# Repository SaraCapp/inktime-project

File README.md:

Schematicul meu este destul de bine organizat si se vede ca am gandit proiectul pe blocuri. Se distinge clar zona de microcontroller, partea de alimentare, zona de debug si fuel gauge-ul, ceea ce face schema mai usor de urmarit. Per total consider ca are o structura logica si se intelege destul de bine cum comunica componentele intre ele.
Proiectul meu este un dispozitiv bazat pe nRF52840. Acesta controleaza mai multe componente precum display-ul e-paper, IMU-ul, partea de haptic si fuel gauge-ul pentru baterie.
Componenta principala este nRF52840. Acesta comunica cu restul componentelor si controleaza functionarea intregului sistem.
Blocurile principale din proiect sunt:
- nRF52840
- display e-paper
- IMU
- haptic driver
- fuel gauge
- power management
- baterie Li-Po
- USB-C
Fisierele gerber bom si pick and place se gasesc in manufacturing
nRF52840 este conectat la componente prin interfete de tip I2C, SPI, GPIO si SWD.

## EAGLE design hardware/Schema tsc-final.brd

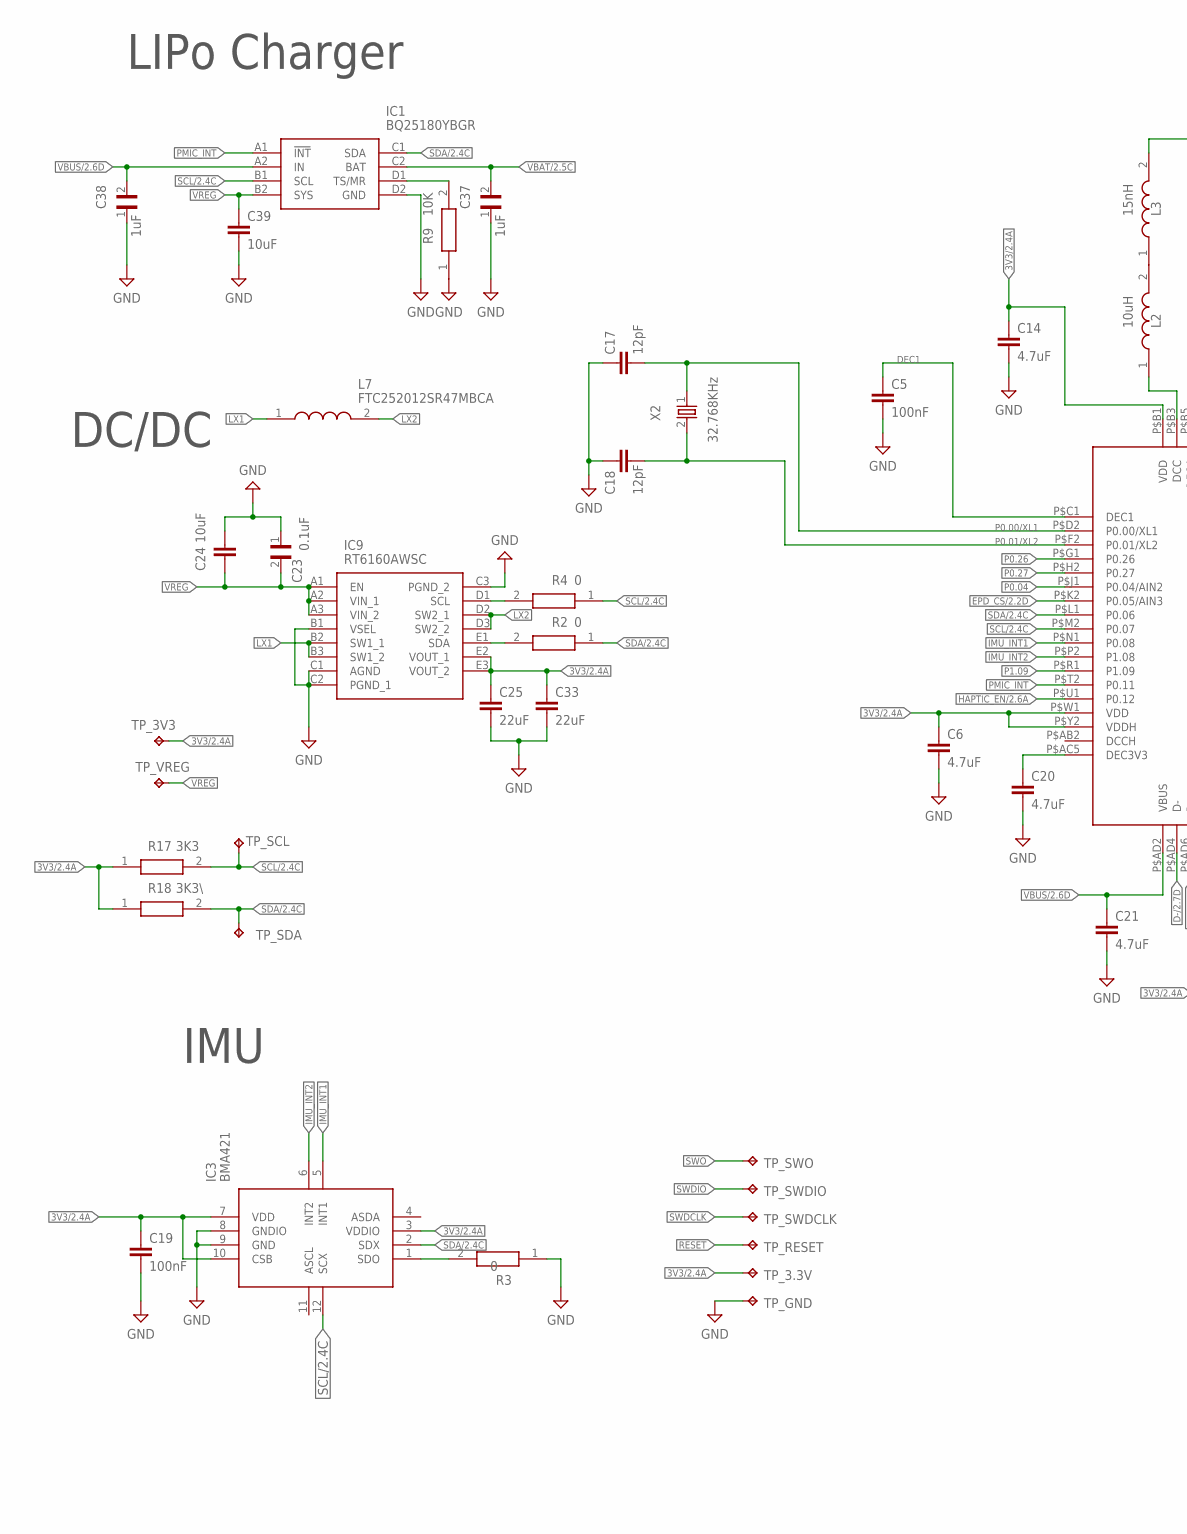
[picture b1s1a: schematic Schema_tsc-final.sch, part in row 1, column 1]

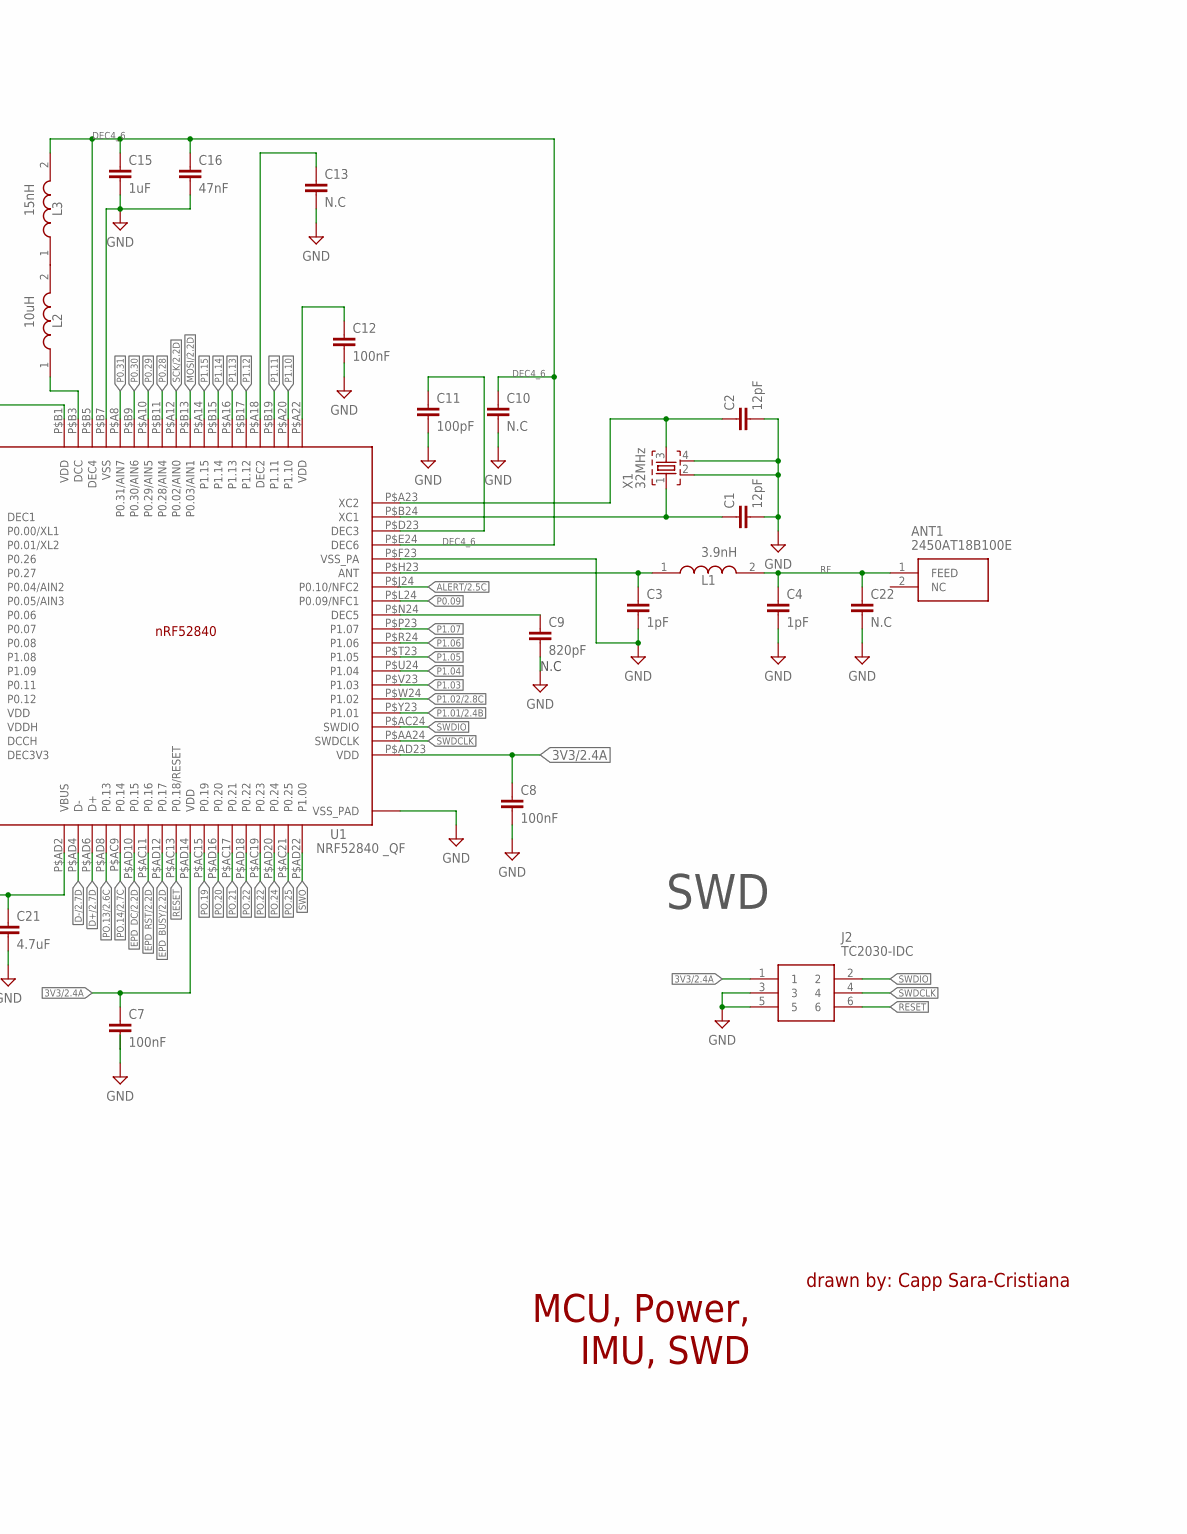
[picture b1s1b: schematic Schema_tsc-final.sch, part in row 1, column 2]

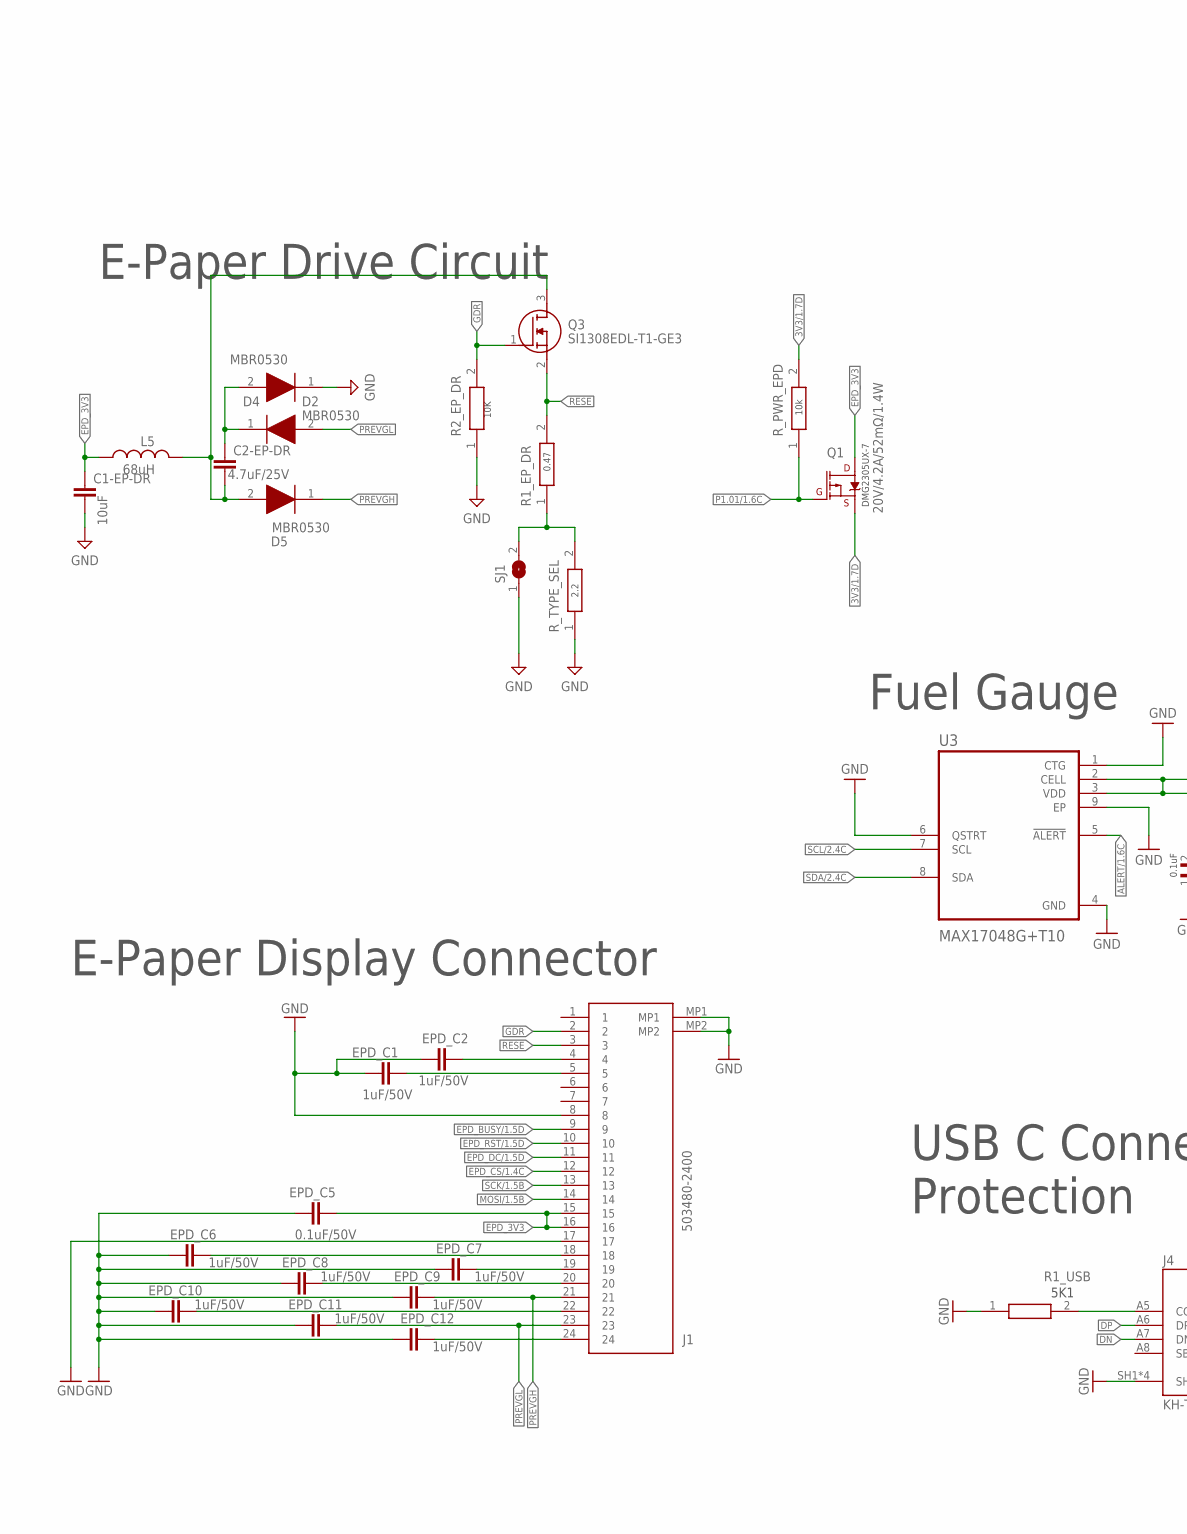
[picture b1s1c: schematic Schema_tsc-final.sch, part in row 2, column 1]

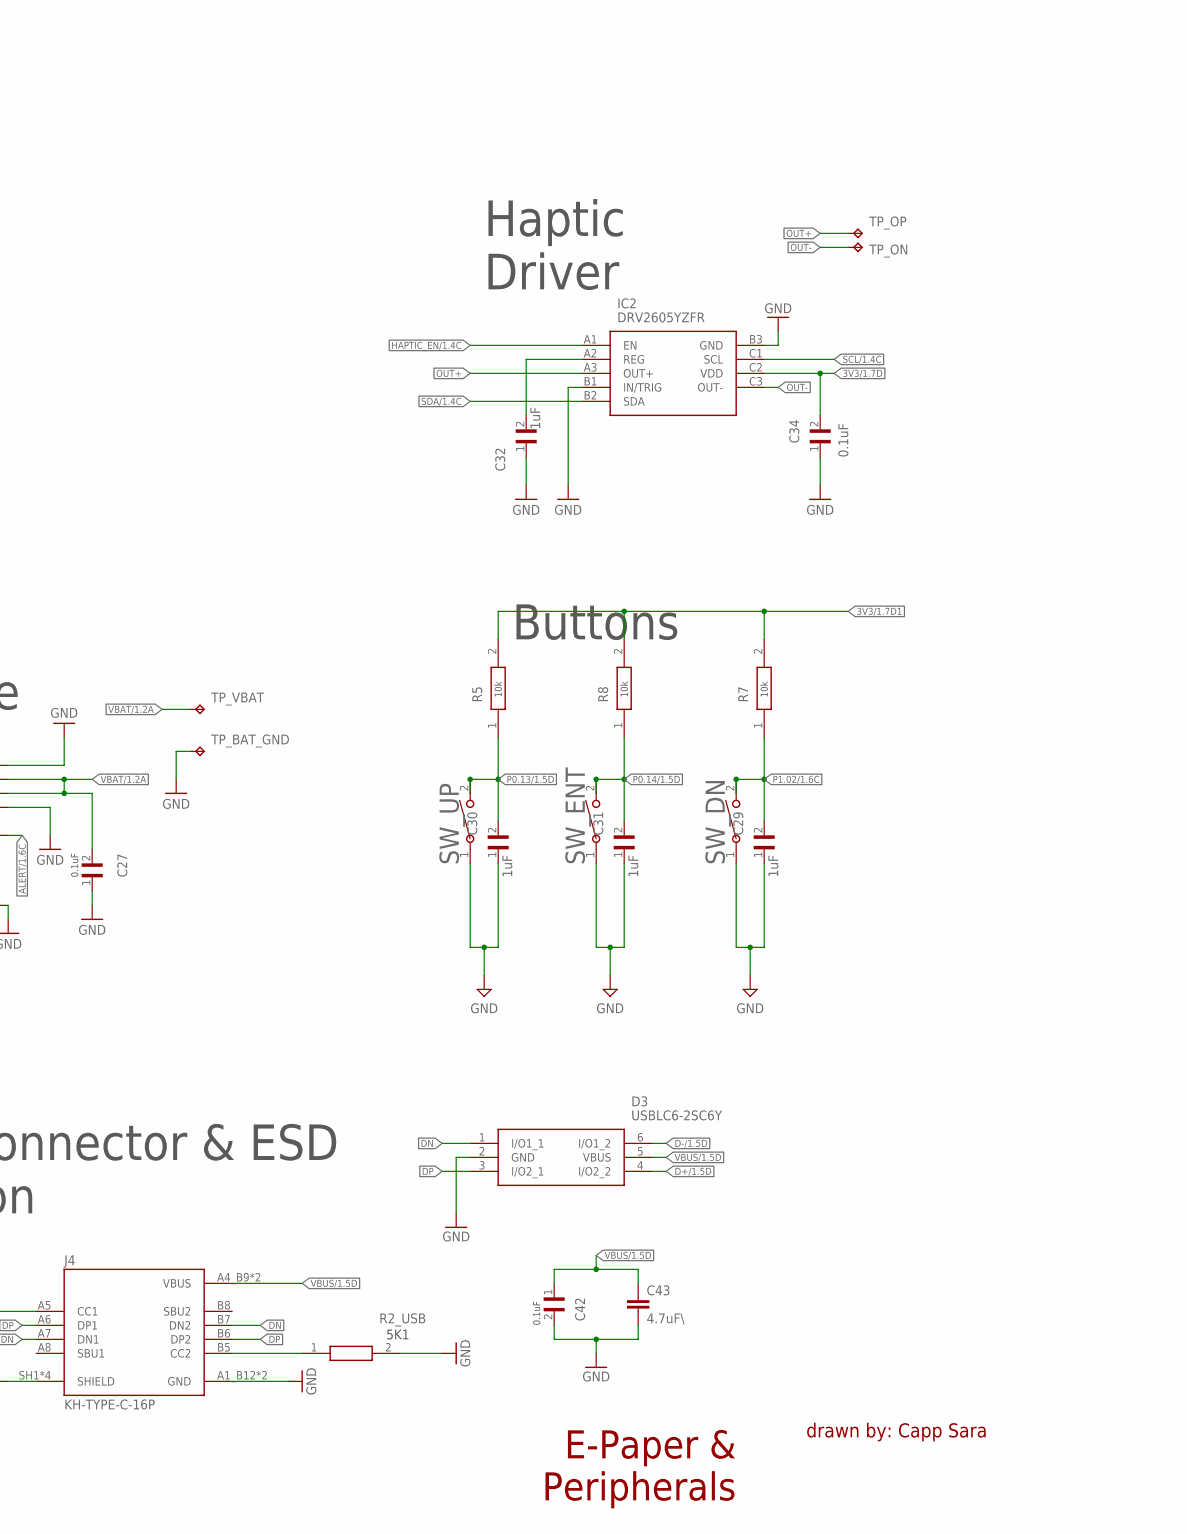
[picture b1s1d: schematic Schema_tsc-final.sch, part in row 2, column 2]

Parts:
ANT1: 2450AT18B100E; 2450AT18B100E_ANTC3216X140N
C1, C2, C17, C18: 12pF; NORDIC_NRF_3_RESC0201_L
C1-EP-DR, C24, C39: 10uF; NORDIC_NRF_3_RESC0402_L
C2-EP-DR: 4.7uF/25V; NORDIC_NRF_3_RESC0402_L
C3, C4: 1pF; NORDIC_NRF_3_RESC0201_L
C5, C7, C8, C12, C19: 100nF; NORDIC_NRF_3_RESC0201_L
C6, C14, C20, C21: 4.7uF; NORDIC_NRF_3_RESC0402_L
C9: 820pF; NORDIC_NRF_3_RESC0201_L
C10, C13: N.C; NORDIC_NRF_3_RESC0201_L
C11: 100pF; NORDIC_NRF_3_RESC0201_L
C15: 1uF; NORDIC_NRF_3_RESC0402_L
C16: 47nF; NORDIC_NRF_3_RESC0201_L
C22: N.C; NORDIC_NRF_3_RESC0402_L
C23, C42: 0.1uF; GRM011R60J152KE01L_2_CAPC0201X13N
C25, C33: 22uF; NORDIC_NRF_3_RESC0402_L
C27, C34: 0.1uF; GRM011R60J152KE01L_1_0201
C29, C30, C31, C37, C38: 1uF; GRM011R60J152KE01L_2_CAPC0201X13N
C32: 1uF; GRM011R60J152KE01L_1_0201
C43: 4.7uF\; NORDIC_NRF_3_RESC0402_L
D2, D4, D5: MBR0530; ESP32_C6_LIBRARY_5_SOD3716X135N
D3: USBLC6-2SC6Y; ESP32_C6_LIBRARY_3_SOT95P280X145-6N
EPD_C1, EPD_C2, EPD_C6, EPD_C7, EPD_C8, EPD_C9, EPD_C10, EPD_C11, EPD_C12: 1uF/50V; NORDIC_NRF_3_RESC0402_L
EPD_C5: 0.1uF/50V; NORDIC_NRF_3_RESC0201_L
IC1: BQ25180YBGR; BQ25180YBGR_BGA8C40P2X4_100X155X50
IC2: DRV2605YZFR; DRV2605YZFR_BGA9C50P3X3_144X144X62
IC3: BMA421; BMA423_BMA423
IC9: RT6160AWSC; RT6160AWSC_BGA15C40P3X5_140X230X60
J1: 503480-2400; 503480-2400_5034802400
J2: TC2030-IDC; TC2030-IDC_TC2030IDC
J4: KH-TYPE-C-16P; KH-TYPE-C-16P_KINGHELM_KH-TYPE-C-16P
L1: 3.9nH; MLP2016SR47MT0S1_INDC2016X100N
L2: 10uH; MLP2016SR47MT0S1_INDC2016X100N
L3: 15nH; MLP2016SR47MT0S1_INDC2016X100N
L5: 68uH; NORDIC_NRF_2_RESC0402_L
L7: FTC252012SR47MBCA; MLP2016SR47MT0S1_INDC2016X100N
Q1: 20V/4.2A/52mΩ/1.4W; ESP32_C6_LIBRARY_4_ESP32_C6_LIBRARY_4_ESP32_C6_LIBRARY_4_ES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
Q3: SI1308EDL-T1-GE3; ESP32_C6_LIBRARY_6_SOT65P210X110-3N
R1_EP_DR: 0.47; CPF0201D7K68C1_0201
R1_USB, R2_USB: 5K1; CPF0201D7K68C1_0201
R2, R3, R4: 0; CPF0201D7K68C1_0201
R2_EP_DR, R5, R7, R8, R9: 10K; CPF0201D7K68C1_0201
R17: 3K3; CPF0201D7K68C1_0201
R18: 3K3\; CPF0201D7K68C1_0201
R_PWR_EPD: 10K; CPF0201D7K68C1_0201
R_TYPE_SEL: 2.2; CPF0201D7K68C1_0201
SJ1: ESP32_C6_LIBRARY_7_JUMPER_SJ
SW_DN: 2025-10-22_07-23-44_LIBRARY_EVP-AKE31ASW_EVP-AKE3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; 2025-10-22_07-23-44_LIBRARY_SW_EVP-AKE31A_PAN
SW_ENT: 2025-10-22_07-23-44_LIBRARY_EVP-AKE31ASW_EVP-AKE3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; 2025-10-22_07-23-44_LIBRARY_SW_EVP-AKE31A_PAN
SW_UP: 2025-10-22_07-23-44_LIBRARY_EVP-AKE31ASW_EVP-AKE3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; 2025-10-22_07-23-44_LIBRARY_SW_EVP-AKE31A_PAN
TP_3.3V, TP_3V3: HECTOR_WATCH_1_TPTP20R; HECTOR_WATCH_1_TP20R
TP_BAT_GND: HECTOR_WATCH_1_TPTP20R; HECTOR_WATCH_1_TP20R
TP_GND: HECTOR_WATCH_1_TPTP20R; HECTOR_WATCH_1_TP20R
TP_ON: HECTOR_WATCH_1_TPTP20R; HECTOR_WATCH_1_TP20R
TP_OP: HECTOR_WATCH_1_TPTP20R; HECTOR_WATCH_1_TP20R
TP_RESET: HECTOR_WATCH_1_TPTP20R; HECTOR_WATCH_1_TP20R
TP_SCL: HECTOR_WATCH_1_TPTP20R; HECTOR_WATCH_1_TP20R
TP_SDA: HECTOR_WATCH_1_TPTP20R; HECTOR_WATCH_1_TP20R
TP_SWDCLK: HECTOR_WATCH_1_TPTP20R; HECTOR_WATCH_1_TP20R
TP_SWDIO: HECTOR_WATCH_1_TPTP20R; HECTOR_WATCH_1_TP20R
TP_SWO: HECTOR_WATCH_1_TPTP20R; HECTOR_WATCH_1_TP20R
TP_VBAT: HECTOR_WATCH_1_TPTP20R; HECTOR_WATCH_1_TP20R
TP_VREG: HECTOR_WATCH_1_TPTP20R; HECTOR_WATCH_1_TP20R
U1: NRF52840 _QF; NORDIC_NRF_4_AQFN50P700X700X85_HS-74N
U3: MAX17048G+T10; ESP32_C6_LIBRARY_SON50P200X200X80-9N
X1: 32MHz; NORDIC_NRF_BT-XTAL_2016_N
X2: 32.768KHz; NORDIC_NRF_1_XTAL_3215_N

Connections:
3V3/1.7D: C34.2, IC2.C2 (VDD), Q1.2 (S), R_PWR_EPD.2
3V3/1.7D1: R5.2, R7.2, R8.2
3V3/2.4A: C6.1, C7.1, C8.1, C19.1, C25.1, C33.1, IC3.3 (VDDIO), IC3.7 (VDD), IC3.10 (CSB), IC9.E2 (VOUT_1), IC9.E3 (VOUT_2), J2.1, TP_3.3V.TP, TP_3V3.TP, U1.P$AD14 (VDD), U1.P$AD23 (VDD), U1.P$W1 (VDD), U1.P$Y2 (VDDH)
ALERT/1.6C: U3.5 (!ALERT)
ALERT/2.5C: U1.P$J24 (P0.10/NFC2)
D+/1.5D: D3.4 (I/O2_2)
D+/2.7D: U1.P$AD6 (D+)
D-/1.5D: D3.6 (I/O1_2)
D-/2.7D: U1.P$AD4 (D-)
DEC1: C5.1, U1.P$C1 (DEC1)
DEC4_6: C10.1, C15.1, C16.1, L3.2, U1.P$B5 (DEC4), U1.P$E24 (DEC6)
DN: D3.1 (I/O1_1), J4.A7 (DN1), J4.B7 (DN2)
DP: D3.3 (I/O2_1), J4.A6 (DP1), J4.B6 (DP2)
EPD_3V3: C1-EP-DR.1, EPD_C5.2, J1.15, J1.16, L5.1, Q1.3 (D)
EPD_BUSY/1.5D: J1.9
EPD_BUSY/2.2D: U1.P$AD12 (P0.17)
EPD_CS/1.4C: J1.12
EPD_CS/2.2D: U1.P$K2 (P0.05/AIN3)
EPD_DC/1.5D: J1.11
EPD_DC/2.2D: U1.P$AD10 (P0.15)
EPD_RST/1.5D: J1.10
EPD_RST/2.2D: U1.P$AC11 (P0.16)
GDR: J1.2, Q3.1 (G), R2_EP_DR.2
GND: C1.2, C1-EP-DR.2, C2.2, C3.2, C4.2, C5.2, C6.2, C7.2, C8.2, C9.2, C10.2, C11.2, C12.2, C13.2, C14.2, C15.2, C16.2, C17.1, C18.1, C19.2, C20.2, C21.2, C22.2, C23.1, C24.1, C25.2, C27.1, C29.1, C30.1, C31.1, C32.1, C33.2, C34.1, C37.1, C38.1, C39.2, C42.2, C43.2, D3.2 (GND), D4.1 (K), EPD_C1.1, EPD_C2.1, EPD_C5.1, EPD_C6.1, EPD_C7.1, EPD_C8.1, EPD_C9.1, EPD_C10.1, EPD_C11.1, EPD_C12.1, IC1.D2 (GND), IC2.B1 (IN/TRIG), IC2.B3 (GND), IC3.8 (GNDIO), IC3.9 (GND), IC9.B1 (VSEL), IC9.C1 (AGND), IC9.C2 (PGND_1), IC9.C3 (PGND_2), J1.8, J1.17, J1.MP1, J1.MP2, J2.3, J2.5, J4.A1_B12 (GND), J4.A12_B1 (GND), J4.SH1 (SHIELD), J4.SH2 (SHIELD), J4.SH3 (SHIELD), J4.SH4 (SHIELD), R1_USB.1, R2_EP_DR.1, R2_USB.2, R3.1, R9.1, R_TYPE_SEL.1, SJ1.1, SW_DN.1, SW_ENT.1, SW_UP.1, TP_BAT_GND.TP, TP_GND.TP, U1.P$74 (VSS_PAD), U1.P$75 (VSS_PAD), U1.P$76 (VSS_PAD), U1.P$77 (VSS_PAD), U1.P$78 (VSS_PAD), U1.P$79 (VSS_PAD), U1.P$80 (VSS_PAD), U1.P$81 (VSS_PAD), U1.P$82 (VSS_PAD), U1.P$83 (VSS_PAD), U1.P$84 (VSS_PAD), U1.P$85 (VSS_PAD), U1.P$86 (VSS_PAD), U1.P$87 (VSS_PAD), U1.P$88 (VSS_PAD), U1.P$89 (VSS_PAD), U1.P$90 (VSS_PAD), U1.P$B7 (VSS), U1.P$F23 (VSS_PA), U3.1 (CTG), U3.4 (GND), U3.6 (QSTRT), U3.9 (EP), X1.2, X1.4
HAPTIC_EN/1.4C: IC2.A1 (EN)
HAPTIC_EN/2.6A: U1.P$U1 (P0.12)
IMU_INT1: IC3.5 (INT1), U1.P$N1 (P0.08)
IMU_INT2: IC3.6 (INT2), U1.P$P2 (P1.08)
LX1: IC9.B2 (SW1_1), IC9.B3 (SW1_2), L7.1
LX2: IC9.D2 (SW2_1), IC9.D3 (SW2_2), L7.2
MOSI/1.5B: J1.14
MOSI/2.2D: U1.P$B13 (P0.03/AIN1)
unnamed: C11.1, U1.P$D23 (DEC3)
unnamed: C3.1, L1.1, U1.P$H23 (ANT)
unnamed: C1.1, U1.P$B24 (XC1), X1.1
unnamed: C2.1, U1.P$A23 (XC2), X1.3
unnamed: C20.1, U1.P$AC5 (DEC3V3)
unnamed: C9.1, U1.P$N24 (DEC5)
unnamed: C14.1, U1.P$B1 (VDD)
unnamed: L2.1, U1.P$B3 (DCC)
unnamed: L2.2, L3.1
unnamed: C13.1, U1.P$A18 (DEC2)
unnamed: C12.1, U1.P$A22 (VDD)
unnamed: IC3.1 (SDO), R3.2
unnamed: IC9.D1 (SCL), R4.2
unnamed: IC9.E1 (SDA), R2.2
unnamed: R17.1, R18.1
unnamed: IC1.D1 (TS/MR), R9.2
unnamed: C2-EP-DR.2, D5.2 (A), L5.2, Q3.3 (D)
unnamed: C2-EP-DR.1, D2.1 (K), D4.2 (A)
unnamed: R1_EP_DR.1, R_TYPE_SEL.2, SJ1.2
unnamed: EPD_C2.2, J1.4
unnamed: EPD_C1.2, J1.5
unnamed: EPD_C6.2, J1.18
unnamed: EPD_C7.2, J1.19
unnamed: EPD_C8.2, J1.20
unnamed: EPD_C10.2, J1.22
unnamed: EPD_C12.2, J1.24
unnamed: C32.2, IC2.A2 (REG)
unnamed: J4.A5 (CC1), R1_USB.2
unnamed: J4.B5 (CC2), R2_USB.1
OUT+: IC2.A3 (OUT+), TP_OP.TP
OUT-: IC2.C3 (OUT-), TP_ON.TP
P0.00/XL1: C17.2, U1.P$D2 (P0.00/XL1), X2.1
P0.01/XL2: C18.2, U1.P$F2 (P0.01/XL2), X2.2
P0.04: U1.P$J1 (P0.04/AIN2)
P0.09: U1.P$L24 (P0.09/NFC1)
P0.13/1.5D: C30.2, R5.1, SW_UP.2
P0.14/1.5D: C31.2, R8.1, SW_ENT.2
P0.26: U1.P$G1 (P0.26)
P0.27: U1.P$H2 (P0.27)
P0.28: U1.P$B11 (P0.28/AIN4)
P0.29: U1.P$A10 (P0.29/AIN5)
P0.30: U1.P$B9 (P0.30/AIN6)
P0.31: U1.P$A8 (P0.31/AIN7)
P1.01/1.6C: Q1.1 (G), R_PWR_EPD.1
P1.01/2.4B: U1.P$Y23 (P1.01)
P1.02/1.6C: C29.2, R7.1, SW_DN.2
P1.02/2.8C: U1.P$W24 (P1.02)
P1.03: U1.P$V23 (P1.03)
P1.04: U1.P$U24 (P1.04)
P1.05: U1.P$T23 (P1.05)
P1.06: U1.P$R24 (P1.06)
P1.07: U1.P$P23 (P1.07)
P1.09: U1.P$R1 (P1.09)
P1.10: U1.P$A20 (P1.10)
P1.11: U1.P$B19 (P1.11)
P1.12: U1.P$B17 (P1.12)
P1.13: U1.P$A16 (P1.13)
P1.14: U1.P$B15 (P1.14)
P1.15: U1.P$A14 (P1.15)
PMIC_INT: IC1.A1 (!INT), U1.P$T2 (P0.11)
PO.13/2.6C: U1.P$AD8 (P0.13)
PO.14/2.7C: U1.P$AC9 (P0.14)
PO.19: U1.P$AC15 (P0.19)
PO.20: U1.P$AD16 (P0.20)
PO.21: U1.P$AC17 (P0.21)
PO.22: U1.P$AC19 (P0.23)
PO.24: U1.P$AD20 (P0.24)
PO.25: U1.P$AC21 (P0.25)
PREVGH: D5.1 (K), EPD_C9.2, J1.21
PREVGL: D2.2 (A), EPD_C11.2, J1.23
RESE: J1.3, Q3.2 (S), R1_EP_DR.2
RESET: J2.6, TP_RESET.TP, U1.P$AC13 (P0.18/RESET)
RF: ANT1.1 (FEED), C4.1, C22.1, L1.2
SCK/1.5B: J1.13
SCK/2.2D: U1.P$A12 (P0.02/AIN0)
SCL/1.4C: IC2.C1 (SCL)
SCL/2.4C: IC1.B1 (SCL), IC3.12 (SCX), R4.1, R17.2, TP_SCL.TP, U1.P$M2 (P0.07), U3.7 (SCL)
SDA/1.4C: IC2.B2 (SDA)
SDA/2.4C: IC1.C1 (SDA), IC3.2 (SDX), R2.1, R18.2, TP_SDA.TP, U1.P$L1 (P0.06), U3.8 (SDA)
SWDCLK: J2.4, TP_SWDCLK.TP, U1.P$AA24 (SWDCLK)
SWDIO: J2.2, TP_SWDIO.TP, U1.P$AC24 (SWDIO)
SWO: TP_SWO.TP, U1.P$AD22 (P1.00)
VBAT/1.2A: C27.2, TP_VBAT.TP, U3.2 (CELL), U3.3 (VDD)
VBAT/2.5C: C37.2, IC1.C2 (BAT)
VBUS/1.5D: C42.1, C43.1, D3.5 (VBUS), J4.A4_B9 (VBUS), J4.A9_B4 (VBUS)
VBUS/2.6D: C21.1, C38.2, IC1.A2 (IN), U1.P$AD2 (VBUS)
VREG: C23.2, C24.2, C39.1, IC1.B2 (SYS), IC9.A1 (EN), IC9.A2 (VIN_1), IC9.A3 (VIN_2), TP_VREG.TP

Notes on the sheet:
SWD
IMU
DC/DC
LIPo Charger
E-Paper Drive Circuit
0.47
2.2
10K
DMG2305UX-7
10k
E-Paper Display Connector
Buttons
Haptic Driver
Fuel Gauge
0.1uF
5K1
USB C Connector & ESD Protection
MCU, Power, IMU, SWD
E-Paper & Peripherals
drawn by: Capp Sara-Cristiana
drawn by: Capp Sara
N.C

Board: 2 copper layers, 105 parts (0 on the bottom side), 67 nets, no tracks yet.

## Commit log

2026-04-10 Create LICENSE
2026-04-10 Create schematic

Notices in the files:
parts and their libraries:
COPYRIGHT: Copyright (C) 2025 Ultra Librarian. All rights reserved.
